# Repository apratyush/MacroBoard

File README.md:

# MacroBoard
MacroBoard is a 3D Printed 10 key mechanical switch keypad with 2 rotary encoders, a buzzer, backlight and an OLED display.
Based on Atmega32U4 Microcontroller on an Arduino Pro Micro Development Board.
All of the keys can be programmed to emulate a single keypress or a combination of keys( eg: CTRL+ALT+DEL, WIN+PRTSC ).
The encoders can also be programmed to send a specific keypress (eg: volume control, media control).

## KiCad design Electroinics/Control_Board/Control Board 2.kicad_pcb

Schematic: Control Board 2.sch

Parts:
BZ1: Buzzer; MagneticBuzzer_ProSignal_ABI-010-RC
J1: ENC1; JST_XH_B03B-XH-A_1x03_P2.50mm_Vertical
J2: ENC2; JST_XH_B03B-XH-A_1x03_P2.50mm_Vertical
J3: OLED; JST_XH_B04B-XH-A_1x04_P2.50mm_Vertical
J4: ROW; JST_XH_B04B-XH-A_1x04_P2.50mm_Vertical
J5: COL; JST_XH_B03B-XH-A_1x03_P2.50mm_Vertical
J7: Backlight; PinHeader_1x02_P2.54mm_Horizontal
MH1, MH2: M3; MountingHole_3.2mm_M3_DIN965_Pad
Q1: IRF540N; TO-220-3_Vertical
R1, R4, R5, R6, R7, R8, R9: 10k; R_0603_1608Metric_Pad1.05x0.95mm_HandSolder
R2: 100R; R_0603_1608Metric_Pad1.05x0.95mm_HandSolder
R3: 1k; R_0603_1608Metric_Pad1.05x0.95mm_HandSolder
SW1: RESET; SW_Tactile_SKHH_Angled
SW2: Layer; SW_Tactile_SKHH_Angled
U1: ProMicro

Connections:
+5V: J3.2, J7.1, R1.2, R4.2, R5.2, R6.2, R7.2, R8.2, R9.2, U1.21
A0: J4.1, U1.17
A1: J4.2, U1.18
A2: J4.3, U1.19
A3: J4.4, U1.20
D0: J1.1, R6.1, U1.2
D1: J1.2, R7.1, U1.1
D4: J2.2, R8.1, U1.7
D5: J2.3, R9.1, U1.8
D8: R3.1, U1.11
D9: BZ1.1, U1.12
D10: R1.1, SW2.2, U1.13
D14: J5.2, U1.15
D15: J5.3, U1.16
D16: J5.1, U1.14
GND: J1.3, J2.1, J3.1, Q1.3 (S), R2.2, SW1.1, SW2.1, U1.3, U1.4, U1.23
MOSFET: J7.2, Q1.2 (D)
unnamed: BZ1.2, R2.1
unnamed: Q1.1 (G), R3.2
RST: SW1.2, U1.22
SCL: J3.3, R5.1, U1.5
SDA: J3.4, R4.1, U1.6

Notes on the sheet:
ENC1
ENC2
OLED
Layer Button
Buzzer
MOSFET

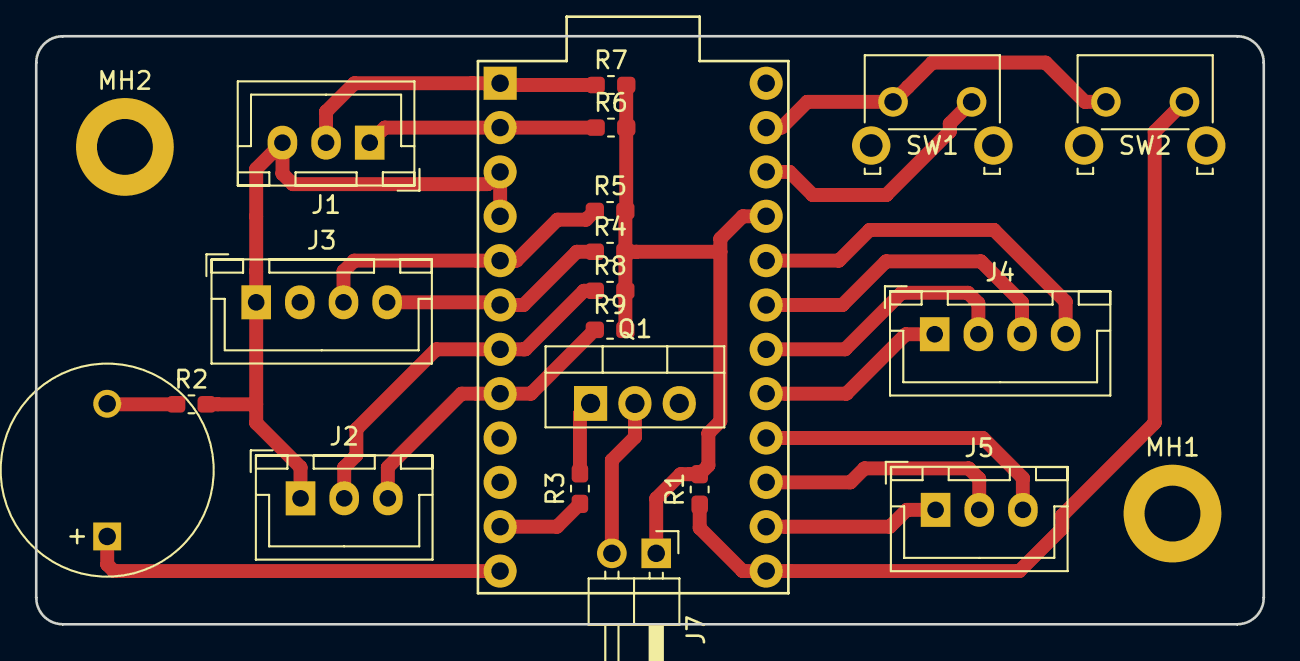
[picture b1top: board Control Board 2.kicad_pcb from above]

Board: 2 copper layers, 70.3 x 33.7 mm, 22 parts (0 on the bottom side), 22 nets.
